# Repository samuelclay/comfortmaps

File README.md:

## PostgreSQL

sudo su postgres -c "pg_ctl -D /usr/local/var/postgres stop" # Stop 9.4
sudo launchctl stop /Library/LaunchDaemons/com.edb.launchd.postgresql-9.4.plist

sudo launchctl load /Library/LaunchDaemons/com.edb.launchd.postgresql-9.4.plist

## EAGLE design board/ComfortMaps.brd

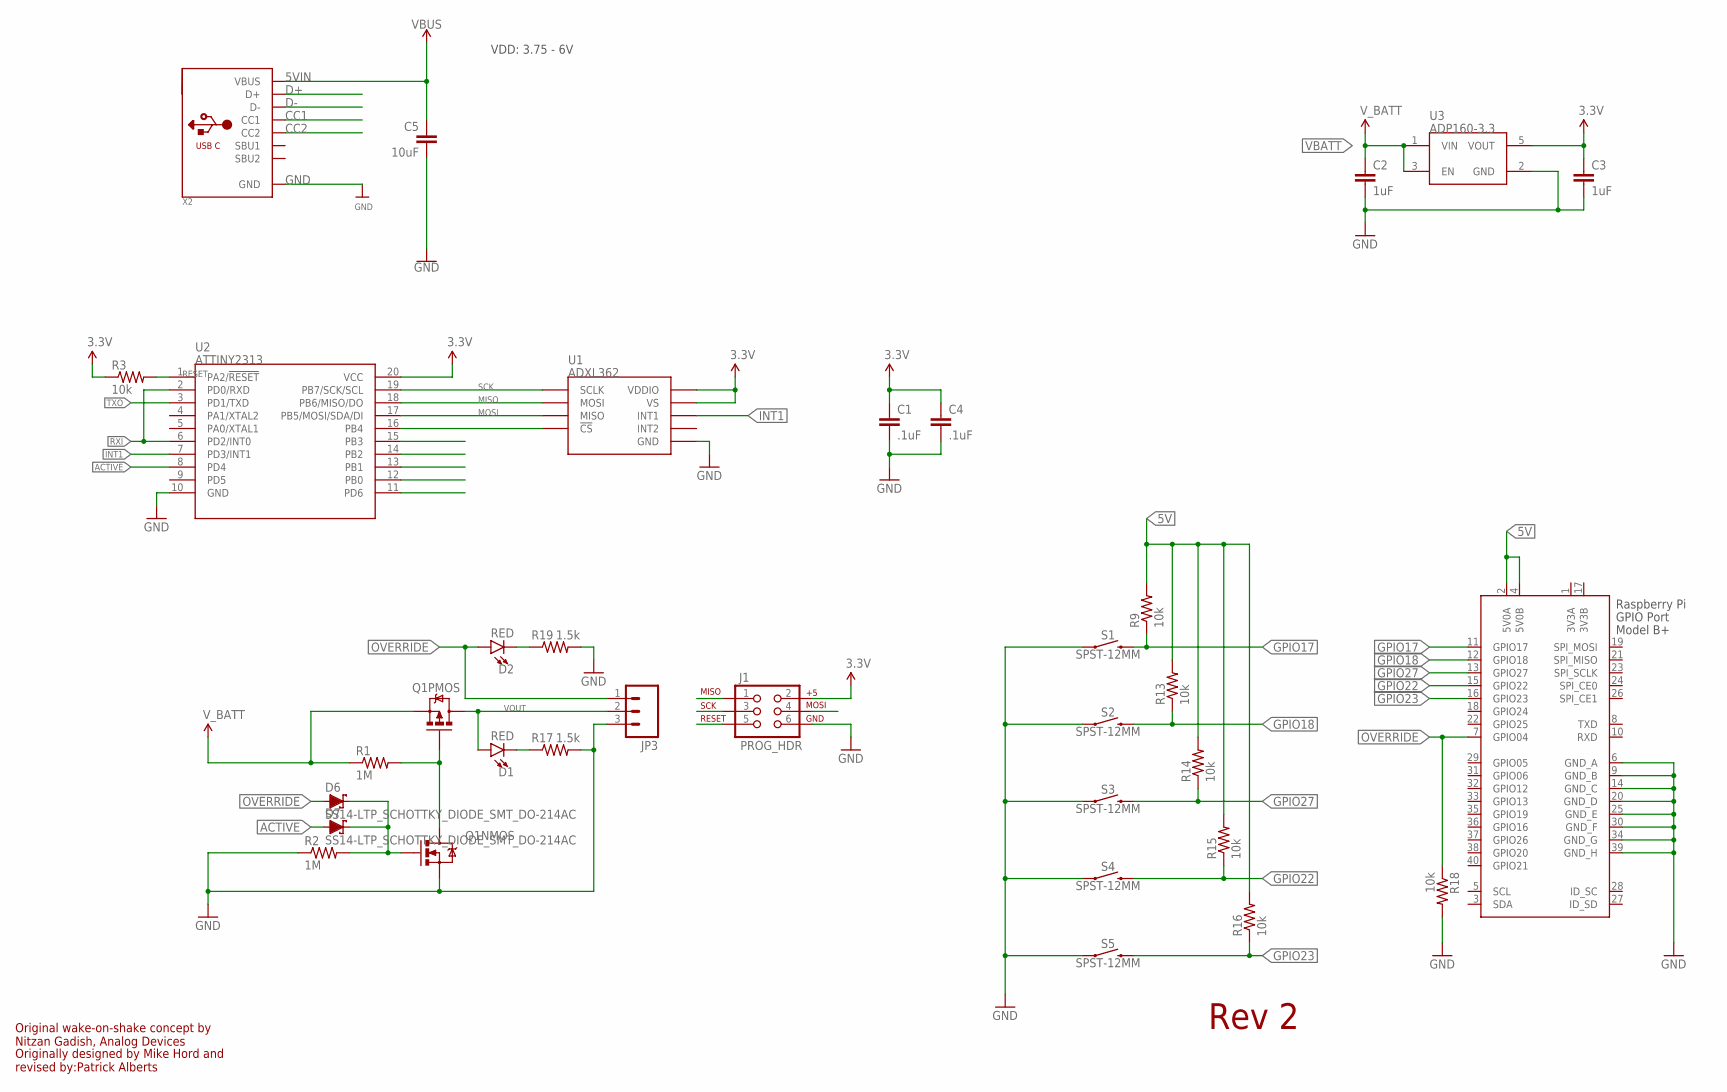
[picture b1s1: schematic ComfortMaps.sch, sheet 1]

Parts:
C1, C4: .1uF; 0603-CAP
C2, C3: 1uF; 0603-CAP
C5: 10uF; 0603
D1, D2: RED; LED-0603
D6, D7: SS14-LTP_SCHOTTKY_DIODE_SMT_DO-214AC; DO-214AC
J1: PROG_HDR; 2X3
JP3: M03PTH; 1X03
Q1: IRF7509; MSOP8
R1, R2: 1M; 0603-RES
R3, R9, R13, R14, R15, R16, R18: 10k; 0603-RES
R17, R19: 1.5k; 0603
S1, S2, S3, S4, S5: SPST-12MM; TACTILE_SWITCH_SMD_12MM
U1: ADXL362; ADXL362-1:1
U2: ATTINY2313; SOP20W
U3: ADP160-3.3; SOT23-5
X1: RASPI_GPIO_B+#_PIN; RASPI_GPIO_B+_PIN
X2: USB_C; USB_C_CUSB31-CFM2AX-01-X

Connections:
3.3V: C1.1, C3.1, C4.1, J1.2, R3.1, U1.P$1 (VDDIO), U1.P$14 (VS), U2.20 (VCC), U3.5 (VOUT)
3V3A: X1.1 (3V3A)
3V3B: X1.17 (3V3B)
5V: R9.2, R13.2, R14.2, R15.2, R16.2, X1.2 (5V0A), X1.4 (5V0B); also elsewhere on the board
5VIN: C5.1, X2.A4B9 (VBUS), X2.B4A9 (VBUS); also elsewhere on the board
ACTIVE: D7.A, U2.8 (PD4)
CC1: X2.A5 (CC1)
CC2: X2.B5 (CC2)
D+: X2.A6 (D+), X2.B6 (D+)
D-: X2.A7 (D-), X2.B7 (D-)
GND: C1.2, C2.2, C3.2, C4.2, C5.2, J1.6, JP3.3, Q1.1 (S), R2.1, R17.2, R18.2, R19.2, S1.1, S1.2 (1), S2.1, S2.2 (1), S3.1, S3.2 (1), S4.1, S4.2 (1), S5.1, S5.2 (1), U1.P$12 (GND), U1.P$13 (GND), U1.P$16 (GND), U2.10 (GND), U3.2 (GND), X1.6 (GND_A), X1.9 (GND_B), X1.14 (GND_C), X1.20 (GND_D), X1.25 (GND_E), X1.30 (GND_F), X1.34 (GND_G), X1.39 (GND_H), X2.A1B12 (GND), X2.B1A12 (GND); also elsewhere on the board
GPIO17: R9.1, S1.3 (2), S1.4 (2), X1.11 (GPIO17)
GPIO18: R13.1, S2.3 (2), S2.4 (2), X1.12 (GPIO18)
GPIO22: R15.1, S4.3 (2), S4.4 (2), X1.15 (GPIO22)
GPIO23: R16.1, S5.3 (2), S5.4 (2), X1.16 (GPIO23)
GPIO27: R14.1, S3.3 (2), S3.4 (2), X1.13 (GPIO27)
INT1: U1.P$11 (INT1), U2.7 (PD3/INT1)
MISO: J1.1, U1.P$6 (MOSI), U2.18 (PB6/MISO/DO)
MOSI: J1.4, U1.P$7 (MISO), U2.17 (PB5/MOSI/SDA/DI)
unnamed: Q1.4 (G), Q1.7 (D), Q1.8 (D), R1.2
unnamed: D6.C, D7.C, Q1.2 (G), R2.2
unnamed: U1.P$8 (!CS), U2.16 (PB4)
unnamed: D1.C, R17.1
unnamed: D2.C, R19.1
OVERRIDE: D2.A, D6.A, JP3.1, R18.1, X1.7 (GPIO04)
RESET: J1.5, R3.2, U2.1 (PA2/!RESET)
RXI: U2.2 (PD0/RXD), U2.6 (PD2/INT0)
SCK: J1.3, U1.P$4 (SCLK), U2.19 (PB7/SCK/SCL)
TXO: U2.3 (PD1/TXD)
VBATT: C2.1, Q1.3 (S), R1.1, U3.1 (VIN), U3.3 (EN); also elsewhere on the board
VOUT: D1.A, JP3.2, Q1.5 (D), Q1.6 (D)

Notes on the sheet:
Rev 2
Original wake-on-shake concept by Nitzan Gadish, Analog Devices
Originally designed by Mike Hord and revised by:Patrick Alberts
VDD: 3.75 - 6V

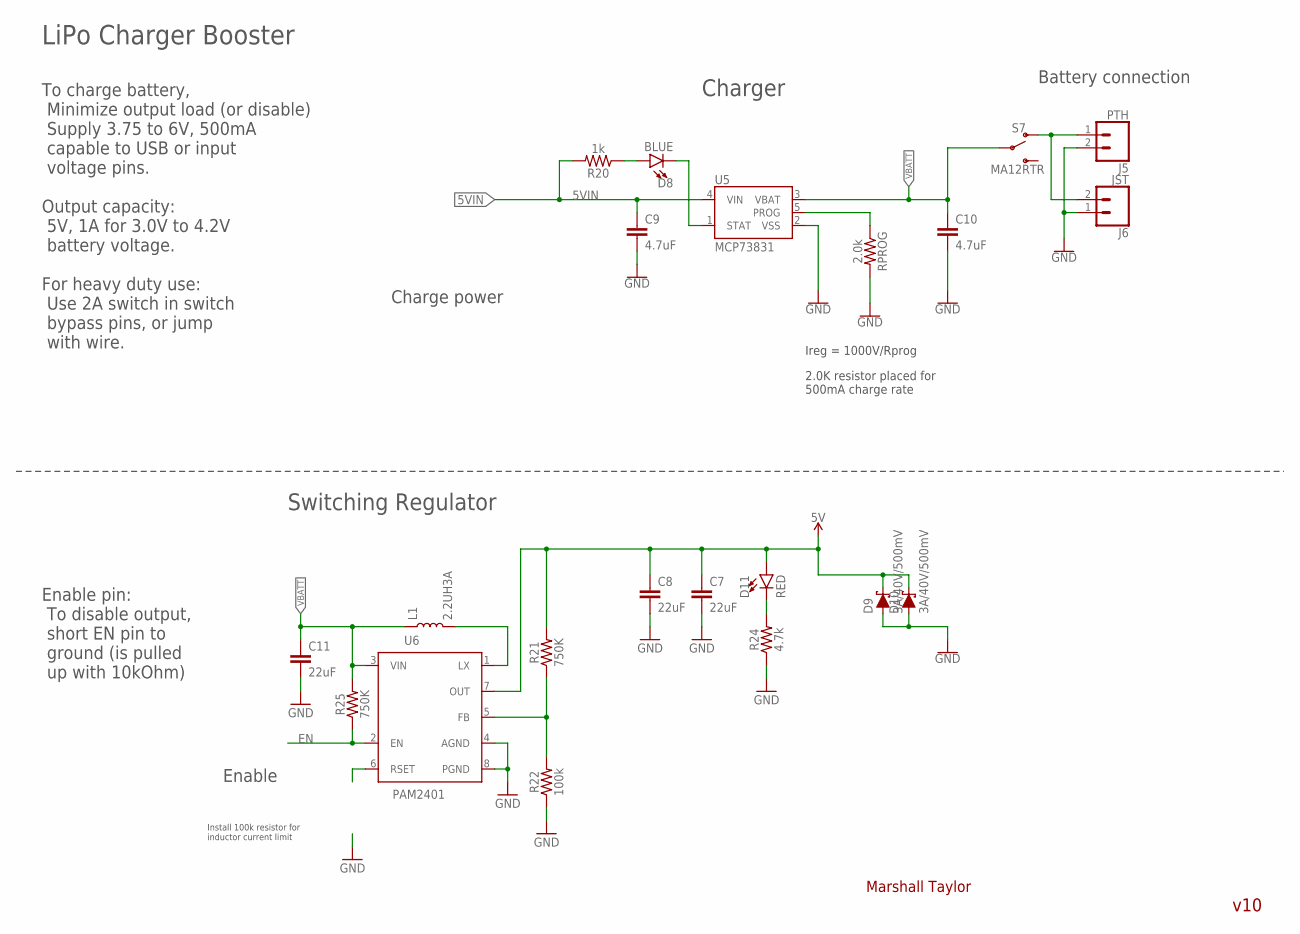
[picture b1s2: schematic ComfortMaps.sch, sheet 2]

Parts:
C7, C8, C11: 22uF; 0805
C9, C10: 4.7uF; 0603
D8: BLUE; LED-0603
D9, D10: 3A/40V/500mV; SMA-DIODE
D11: RED; LED-0603
J5: PTH; 1X02
J6: JST; JST-2-SMD
L1: 2.2UH3A; INDUCTOR_4X4MM
R20: 1k; 0603
R21, R25: 750K; 0603
R22: 100k; 0603
R24: 4.7k; 0603
RPROG: 2.0k; 0603
S7: MA12RTR; SWITCH_SPST_SMD_A; DIGIKEY 679-1847-1-ND
U5: MCP73831; SOT23-5
U6: PAM2401; MSOP8

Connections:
5V: C7.1, C8.1, D9.C, D10.C, D11.A, R21.2, U6.7 (OUT); also elsewhere on the board
5VIN: C9.1, R20.2, U5.4 (VIN); also elsewhere on the board
EN: R25.1, U6.2 (EN)
GND: C7.2, C8.2, C9.2, C10.2, C11.2, D9.A, D10.A, J5.2, J6.1 (2), R22.1, R24.1, RPROG.2, U5.2 (VSS), U6.4 (AGND), U6.8 (PGND); also elsewhere on the board
unnamed: J5.1, J6.2 (1), S7.1 (O)
unnamed: RPROG.1, U5.5 (PROG)
unnamed: D8.C, U5.1 (STAT)
unnamed: R21.1, R22.2, U6.5 (FB)
unnamed: L1.P$2 (2), U6.1 (LX)
unnamed: D11.C, R24.2
unnamed: D8.A, R20.1
VBATT: C10.1, C11.1, L1.P$1 (1), R25.2, S7.2, U5.3 (VBAT), U6.3 (VIN); also elsewhere on the board

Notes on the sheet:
Charger
Switching Regulator
Marshall Taylor
v10
2.0K resistor placed for 500mA charge rate
Ireg = 1000V/Rprog
To charge battery, Minimize output load (or disable) Supply 3.75 to 6V, 500mA capable to USB or input voltage pins.
Install 100k resistor for inductor current limit
LiPo Charger Booster
Output capacity: 5V, 1A for 3.0V to 4.2V battery voltage.
Enable pin: To disable output, short EN pin to ground (is pulled up with 10kOhm)
Enable
Charge power
Battery connection
For heavy duty use: Use 2A switch in switch bypass pins, or jump with wire.

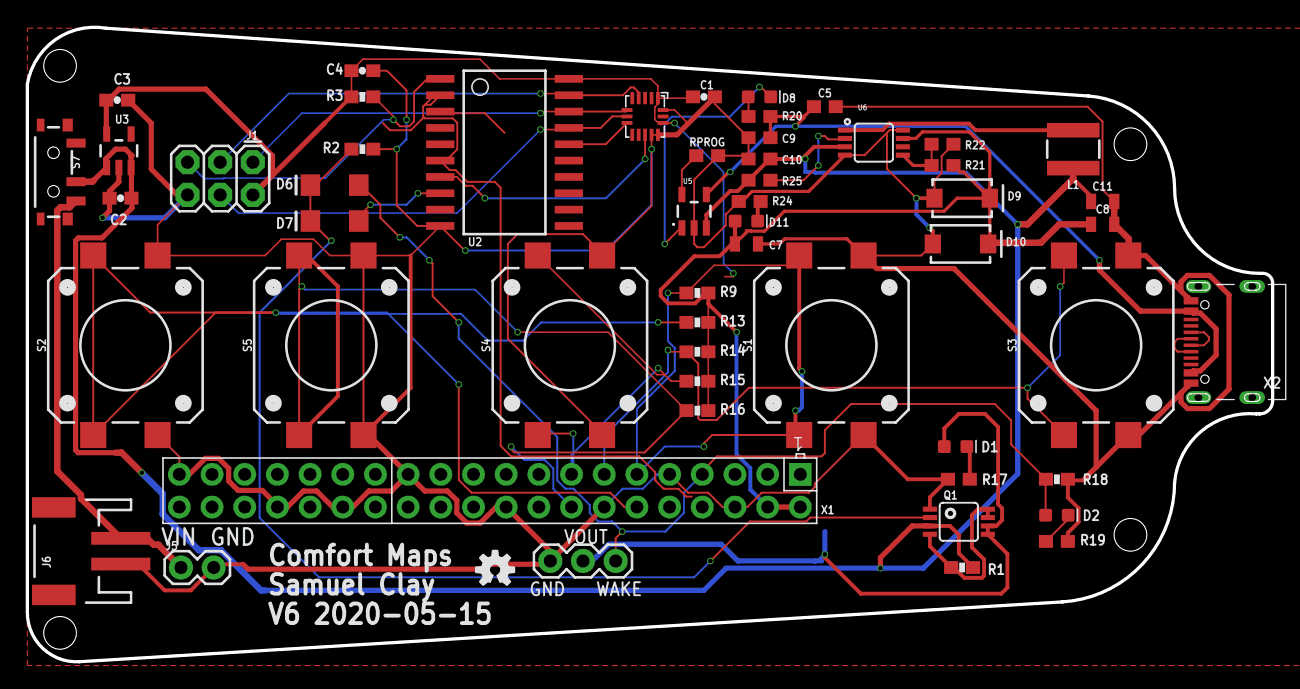
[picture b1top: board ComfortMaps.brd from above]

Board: 2 copper layers, 96.8 x 49.3 mm, 55 parts (0 on the bottom side), 34 nets.

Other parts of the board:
U$3: OSHW-LOGO-S

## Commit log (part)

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2019-10-11 Initial commit, stubbing in snapshots. Needs a login/auth system with just email, then a button UI, then geo.
2019-10-11 Finishing user registration by email only.
2019-10-11 Stubbing in template for record snapshot. Needs geo and db and ajax.
2019-10-12 Storing snapshot ratings. Needs geo.
2019-10-12 Positioning ratings.
2019-10-13 Adding user to pgsql
2019-10-13 Adding password
2019-10-13 Adding nginx.conf.
2019-10-13 Allowed hosts
2019-10-13 Configuring nginx.
2019-10-13 Adding gunicorn socket.
2019-10-13 Minimal UI.
2019-10-13 Icon
2019-10-13 Fixing touch events
2019-10-13 Fixing scroll
2019-10-13 Preventing touch moves.
2019-10-13 Fixing height on orientation change.
2019-10-13 Adding markers on mark.
2019-10-13 Testing distance.
2019-10-13 Reversing heading.
2019-10-13 Correcting distance
2019-10-13 New distance formula.
2019-10-13 25 meters
2019-10-13 Checking distance
2019-10-14 Moving latest marker along.
2019-10-14 Show makrer no amtter what
2019-10-16 Adding map
2019-10-16 Prevent double marking.
2019-11-13 Reorganizing
2019-11-21 Updating board, needs components on digikey.
2019-11-22 Adding BOM with digikey part numbers for everything. Just need the flex cable and short headers.
2019-12-05 Bump django from 2.2.6 to 2.2.8 in /web
    Bumps [django](https://github.com/django/django) from 2.2.6 to 2.2.8.
    - [Release notes](https://github.com/django/django/releases)
    - [Commits](https://github.com/django/django/compare/2.2.6...2.2.8)
2019-12-22 Soldering first board.
2019-12-23 Removing compiled objects.
2019-12-23 Bumping Django
2019-12-24 Prepping for updates to board.
2019-12-28 Latest, before upwork.
2020-01-24 Stubbing in iOS app.
2020-01-24 60 second delay to let the RPi boot.
2020-01-24 Switching to larger schottke diode.
2020-01-28 v3 of the board, with new mounting holes and an added LED for V_out.
2020-01-28 v3 with CAM
2020-02-07 Watching buttons.
2020-02-07 Stubbing in bluetooth manager.
2020-02-08 Adding package.json
2020-02-08 Stubbing in subscription events
2020-02-08 Bluetooth manager handles connection and photo uploading. Seems to work but very slow.
2020-02-08 Finishing up camera bluetooth image upload. Needs to be faster and terminate correctly, but seems to be working.
2020-02-09 Removing breakpoint
2020-02-13 Adding in Wifi manager, but will probably have to wstick with bluetooth because wifi hotspot requires user confirmation.
2020-02-13 Switching to child process for raspistill command.
2020-02-13 Writing raw file, uploading resized thumb. Needs sqlite db and tables for flags on snapshot, uploaded thumb, uploaded raw
2020-02-13 Bump django from 2.2.8 to 2.2.10 in /web
    Bumps [django](https://github.com/django/django) from 2.2.8 to 2.2.10.
    - [Release notes](https://github.com/django/django/releases)
    - [Commits](https://github.com/django/django/compare/2.2.8...2.2.10)
2020-02-13 Removing raspistill module.
2020-02-13 Splitting button and database manager, adding sequelize.
2020-02-13 Fixing button snapshot and stubbing in new snapshot characteristic that notifies of new photo data, leaving photo data to handle uploads.
2020-02-17 Fixing image upload.
2020-02-18 Stubbing in snapshot photo upload
2020-02-18 Fleshing out snapshot characteristic. Both upload correctly now.
2020-02-19 Correct pid/socket fir.
2020-02-19 Creating photos folder if it doesn't exist.
2020-02-20 Adding CocoaPods for Alamofire.
2020-02-20 Who knows what state this is in.
2020-02-20 Moving sock
2020-02-20 Committing most used commands.
2020-02-20 Adding logger
2020-02-20 Adding uploading.
2020-02-20 Adding logging
2020-02-20 Snapshots now save end to end. Need photos.
2020-02-20 Xcode debugging?
2020-02-21 Photo uploads work!
2020-02-21 Adding camera service for ubuntu.
2020-02-23 Attempting to fix background ios app issues.
2020-02-23 Xcode detritus
2020-02-24 Adding vibration
2020-02-24 Refactoring to include counters and stats for notified and uploaded snapshots. Still needs to be decoupled so that photos are uploaded only when the queue is empty.
2020-02-25 Sending batches of photo thumbnails, even as clients reconnect. Somehow sending multiple notifications due to the ending happening multiple times. Need to figure out how to ignore the ending if it's 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
2020-02-25 Handling broken photos
2020-02-26 Adding geojson
2020-02-26 Bump django from 3.0 to 3.0.3 in /web
    Bumps [django](https://github.com/django/django) from 3.0 to 3.0.3.
    - [Release notes](https://github.com/django/django/releases)
    - [Commits](https://github.com/django/django/compare/3.0...3.0.3)
2020-02-27 Adding media
2020-02-27 Adding heatmaps! Terrible point based but it's a start.
2020-02-27 Git f'd up, now gotta recommit.
2020-02-28 JSON gets photo id
2020-02-28 Enlarging spst button pads and connecting both sides.
2020-02-28 New ios icons
2020-02-28 Beginning v4 of board
2020-02-28 Adding platform
2020-02-29 Firmware changes, who knows
2020-02-29 v4 of the PCB. Moved around components for better soldering, added Wake/override led, pulldown on wake.
2020-03-01 Finalizing v4 of board. Moving battery connector so the entire 40 pin connector is solderable and the battery wire no longer gets stuck.
2020-03-03 V5 board, with new usb type c connector and lipo charge controller.
2020-03-18 Latest v5 cam.
2020-03-22 Adding shutdown.js and handling missing camera.
2020-03-23 Adding read/write SD card.
2020-03-26 Updating camera map
2020-03-27 Stubbing in serial reader, which is now unnecessary due to wake on shake checking AWAKE signal from IMU.
2020-03-27 Adding serialport dependency.
2020-03-28 Updating screenshots
2020-03-28 Updating to v5
2020-03-28 Adding speed and course direction. Needs website support.
2020-03-28 Using mph instead of m/s
2020-03-28 Migrations for speed and heading
2020-03-28 Typo in speed
2020-04-06 New homepage
2020-04-06 Renaming raw google map
2020-04-06 Displaying correct data. Now to add scrolling and interactivity. First, interactivity with hovering over active snapshots and then filtering snapshots with a segmented control.
2020-04-07 Adding photo uploaded to geojson.
2020-04-07 photo uploaded migrations.
2020-04-08 Adding broken hover support
2020-04-08 Saving photo width in case I ever change it. Probably should have done this then but who knows.
2020-04-09 Adding scrollspy. Needs filter controls.
2020-04-11 Updating favicon, adding buttons, styling text, stubbing in snapshot photo. Needs activation with vuejs. Then filters.
2020-04-12 Stubbing in dynamic snapshot photo
2020-04-12 Dumping data
2020-04-12 Dynamically updating photo, although the display isn't coming up until the second photo.
2020-04-13 Styling nav.
2020-04-13 Moving around the snapshot photo. Needs filtering.
2020-04-13 Added filters. Would be nice to transition between them which might mean splitting up ratings into separate layers.
2020-04-13 Sizing
2020-04-13 Snapshot detail is always top.
2020-04-14 Flying
2020-04-14 Fixing flying on scroll
2020-04-14 Story section spacing.
2020-04-14 Fixing filter buttons.
2020-04-14 Updating lead paragraph.
2020-04-14 No anonymity
2020-04-14 log user
2020-04-14 Forbidden
2020-04-14 Changing status code.
2020-04-21 Heading arrow
2020-04-21 Adding migrations and models for geocoding. Adding geocode and rating to snapshot detail.
2020-04-21 New filter dropdown icon.
2020-04-22 Refactoring filters
2020-04-22 Adding authentication to map
2020-04-22 Autosaving email hash
2020-04-22 Editing ratings.
2020-04-22 Everyone icon
2020-04-24 Text.
2020-04-24 New logo
2020-04-26 Font and ios logo
2020-04-26 Logo
2020-05-02 Adding map move protector. Doesn't work perfectly yet.
2020-05-03 Adding zoom indicator. Needs interactivity.
2020-05-03 Indicator icon
2020-05-04 Upgrading node (v10.20.1), using later version of bleno.
2020-05-04 Revwerting characteristic id change.
2020-05-04 Updating styles.
2020-05-04 Moving back to older lipo charger.
2020-05-05 Adding faster wakeup pin that runs much quicker.
2020-05-05 Wakeup lasts 90 seconds.
2020-05-05 Adding status bar to app to show camera.
2020-05-06 Better zoom levels.
2020-05-06 Adding explainer text.
2020-05-08 Higher zooms
2020-05-08 Removing box shadow
2020-05-10 Adjusting brand size.
2020-05-10 Fixing zoom scroll.
2020-05-10 Adding last section for overall view.
2020-05-10 Mobile friendly
2020-05-10 Small tweaks to figure.
2020-05-10 Figure doesnt leave for better fades.
2020-05-10 Snapshot icon color.
2020-05-11 Showing all snapshots at first. Also adding fades for snapshot ratings.
2020-05-11 Removing stroke and sticking with more performant circle radius.
2020-05-11 Removing data.
2020-05-11 Fixing updating snapshots.
2020-06-02 v6 board
2020-06-02 Adding photos to iOS
2020-06-02 Fixing sticky snapshot detail view.
2020-06-05 Bump django from 3.0.3 to 3.0.7 in /web
    Bumps [django](https://github.com/django/django) from 3.0.3 to 3.0.7.
    - [Release notes](https://github.com/django/django/releases)
    - [Commits](https://github.com/django/django/compare/3.0.3...3.0.7)
2021-03-19 Bump pillow from 7.0.0 to 8.1.1 in /web
    Bumps [pillow](https://github.com/python-pillow/Pillow) from 7.0.0 to 8.1.1.
    - [Release notes](https://github.com/python-pillow/Pillow/releases)
    - [Changelog](https://github.com/python-pillow/Pillow/blob/master/CHANGES.rst)
    - [Commits](https://github.com/python-pillow/Pillow/compare/7.0.0...8.1.1)
2021-03-30 Bump django from 3.0.3 to 3.0.12 in /web
    Bumps [django](https://github.com/django/django) from 3.0.3 to 3.0.12.
    - [Release notes](https://github.com/django/django/releases)
    - [Commits](https://github.com/django/django/compare/3.0.3...3.0.12)
2021-06-04 Bump django from 3.0.3 to 3.1.9 in /web
    Bumps [django](https://github.com/django/django) from 3.0.3 to 3.1.9.
    - [Release notes](https://github.com/django/django/releases)
    - [Commits](https://github.com/django/django/compare/3.0.3...3.1.9)
    ---
    updated-dependencies:
    - dependency-name: django
2021-06-08 Bump pillow from 7.0.0 to 8.2.0 in /web
    Bumps [pillow](https://github.com/python-pillow/Pillow) from 7.0.0 to 8.2.0.
    - [Release notes](https://github.com/python-pillow/Pillow/releases)
    - [Changelog](https://github.com/python-pillow/Pillow/blob/master/CHANGES.rst)
    - [Commits](https://github.com/python-pillow/Pillow/compare/7.0.0...8.2.0)
    ---
    updated-dependencies:
2021-06-10 Bump django from 3.0.3 to 3.1.12 in /web
    Bumps [django](https://github.com/django/django) from 3.0.3 to 3.1.12.
    - [Release notes](https://github.com/django/django/releases)
    - [Commits](https://github.com/django/django/compare/3.0.3...3.1.12)
    ---
    updated-dependencies:
    - dependency-name: django
2021-09-22 Bump django from 3.0.3 to 3.1.13 in /web
    Bumps [django](https://github.com/django/django) from 3.0.3 to 3.1.13.
    - [Release notes](https://github.com/django/django/releases)
    - [Commits](https://github.com/django/django/compare/3.0.3...3.1.13)
    ---
    updated-dependencies:
    - dependency-name: django
2022-01-13 Bump pillow from 7.0.0 to 9.0.0 in /web
    Bumps [pillow](https://github.com/python-pillow/Pillow) from 7.0.0 to 9.0.0.
    - [Release notes](https://github.com/python-pillow/Pillow/releases)
    - [Changelog](https://github.com/python-pillow/Pillow/blob/main/CHANGES.rst)
    - [Commits](https://github.com/python-pillow/Pillow/compare/7.0.0...9.0.0)
    ---
    updated-dependencies:
2022-06-01 Bump sharp from 0.24.0 to 0.30.5 in /camera
    Bumps [sharp](https://github.com/lovell/sharp) from 0.24.0 to 0.30.5.
    - [Release notes](https://github.com/lovell/sharp/releases)
    - [Changelog](https://github.com/lovell/sharp/blob/main/docs/changelog.md)
    - [Commits](https://github.com/lovell/sharp/compare/v0.24.0...v0.30.5)
    ---
    updated-dependencies:

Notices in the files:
parts and their libraries:
SparkFun-DiscreteSemi: Licensing: CC v3.0 Share-Alike You are welcome to use this library for commercial purposes.
SparkFun-LED: Licensing: Creative Commons ShareAlike 4.0 International - https://creativecommons.org/licenses/by-sa/4.0
